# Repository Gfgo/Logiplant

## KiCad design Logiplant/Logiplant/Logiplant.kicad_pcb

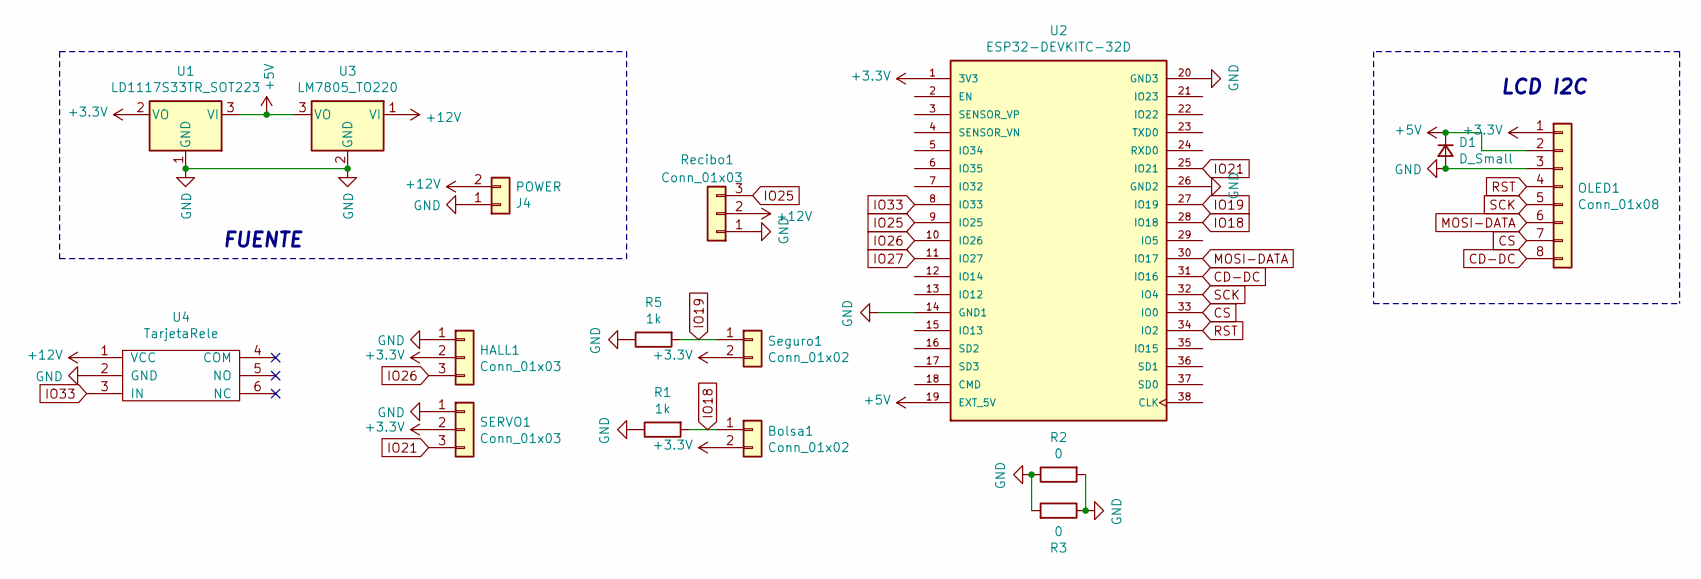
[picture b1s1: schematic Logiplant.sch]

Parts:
Bolsa1: Conn_01x02; PinHeader_1x02_P2.54mm_Vertical
D1: D_Small; D_A-405_P5.08mm_Vertical_KathodeUp
HALL1: Conn_01x03; PinHeader_1x03_P2.54mm_Vertical
J4: POWER; TerminalBlock_Phoenix_MKDS-1,5-2-5.08_1x02_P5.08mm_Horizont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
OLED1: Conn_01x08; OLED128X128
R1, R5: 1k; R_Axial_DIN0207_L6.3mm_D2.5mm_P5.08mm_Vertical
R2, R3: 0; R_Axial_DIN0207_L6.3mm_D2.5mm_P10.16mm_Horizontal
Recibo1: Conn_01x03; TerminalBlock_Phoenix_MKDS-1,5-3-5.08_1x03_P5.08mm_Horizont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
SERVO1: Conn_01x03; PinHeader_1x03_P2.54mm_Vertical
Seguro1: Conn_01x02; PinHeader_1x02_P2.54mm_Vertical
U1: LD1117S33TR_SOT223; TO-220-3_Vertical
U2: ESP32-DEVKITC-32D; Esp32wroverD; PARTREV 4
U3: LM7805_TO220; TO-220-3_Vertical
U4: TarjetaRele; TerminalBlock_Phoenix_MKDS-1,5-3-5.08_1x03_P5.08mm_Horizont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

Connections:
+3V3: Bolsa1.2, HALL1.2, OLED1.1, SERVO1.2, Seguro1.2, U1.2 (VO), U2.1 (3V3)
+5V: D1.1 (K), OLED1.2, U1.3 (VI), U2.19 (EXT_5V), U3.3 (VO)
+12V: J4.2, Recibo1.2, U3.1 (VI), U4.1 (VCC)
CD-DC: OLED1.8, U2.31 (IO16)
CS: OLED1.7, U2.33 (IO0)
GND: D1.2 (A), HALL1.1, J4.1, OLED1.3, R1.1, R2.1, R2.2, R3.1, R3.2, R5.1, Recibo1.1, SERVO1.1, U1.1 (GND), U2.14 (GND1), U2.20 (GND3), U2.26 (GND2), U3.2 (GND), U4.2 (GND)
IO18: Bolsa1.1, R1.2, U2.28 (IO18)
IO19: R5.2, Seguro1.1, U2.27 (IO19)
IO21: SERVO1.3, U2.25 (IO21)
IO25: Recibo1.3, U2.9 (IO25)
IO26: HALL1.3, U2.10 (IO26)
IO27: U2.11 (IO27)
IO33: U2.8 (IO33), U4.3 (IN)
MOSI-DATA: OLED1.6, U2.30 (IO17)
RST: OLED1.4, U2.34 (IO2)
SCK: OLED1.5, U2.32 (IO4)

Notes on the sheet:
LCD I2C
FUENTE

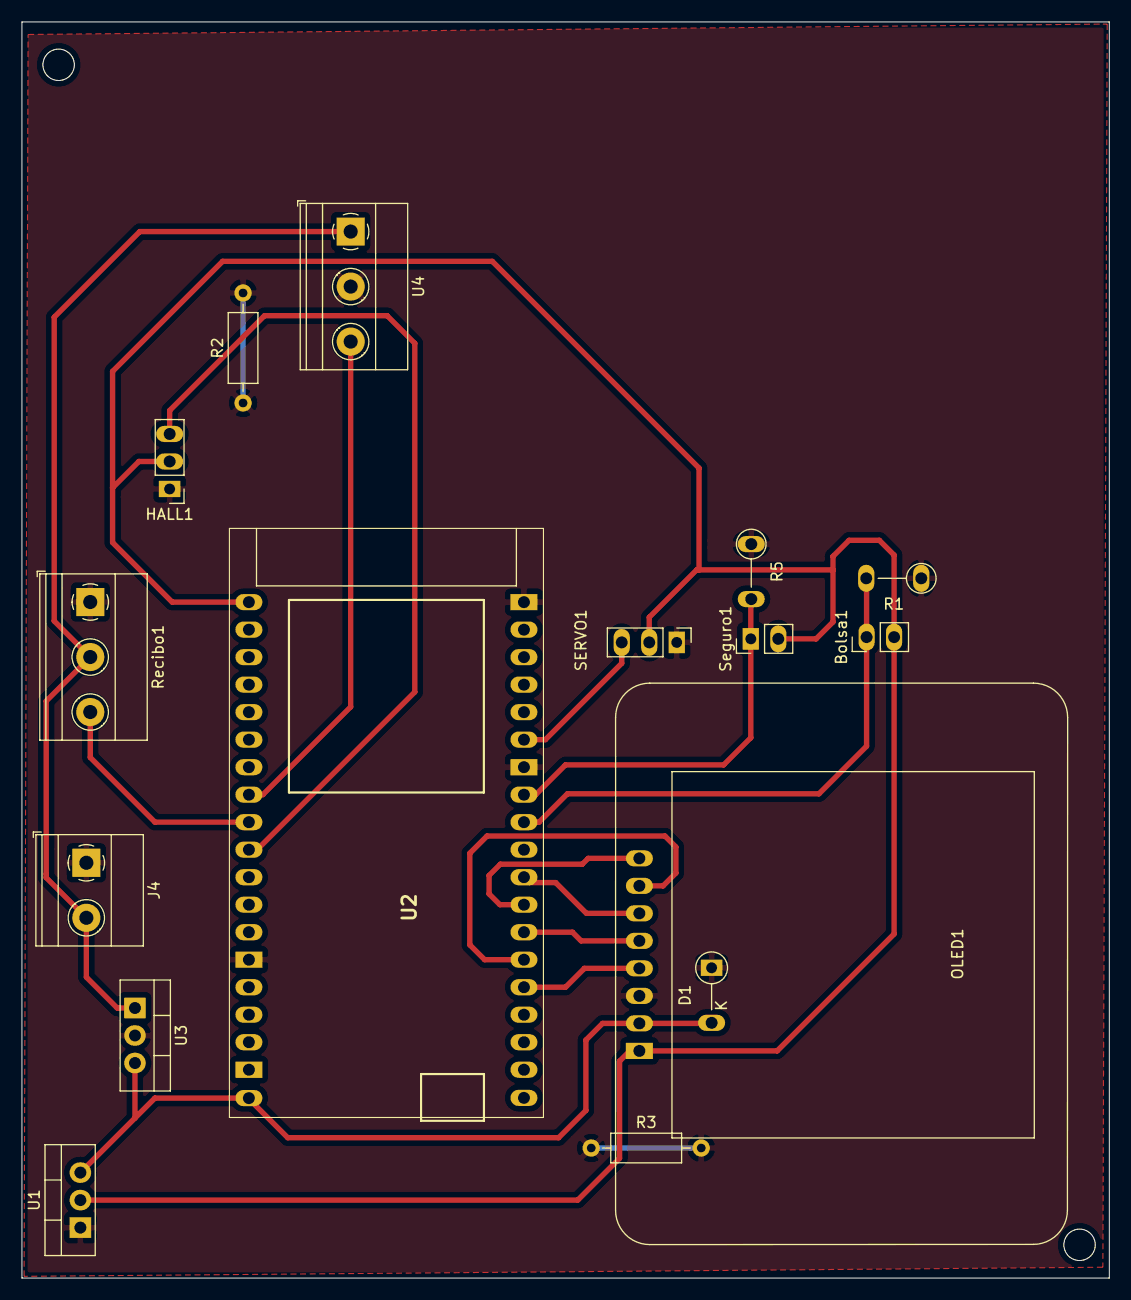
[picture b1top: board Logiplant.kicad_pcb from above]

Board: 2 copper layers, 100.4 x 116.0 mm, 16 parts (0 on the bottom side), 15 nets.

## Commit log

2022-08-02 Create Logiplant.ino
    Inicio
2022-08-10 Update Logiplant.ino
    Distancia y vibración
2023-06-20 Nuevo programa
2023-07-26 Cambio de oled
2023-09-12 Nueva regulación
2023-10-25 Nuevo prog
2023-10-26 Update Logiplant.ino
    Nuevo prog 25/10
2023-10-30 Update Logiplant.ino
    Actualización de programa falta probar todo ok y pantalla.
2023-10-31 Nuevo circuito
    Nuevo circuito
2023-11-08 circuito nuevo
    circuito
2023-11-22 Cambios PCB
2023-11-23 Actualización circuito
2024-05-22 actualización 22/05
2024-08-02 Problemas con interrupcion
    Problemas con interrupcion
2024-08-14 cambios en codigo
    cambios en codigo
2024-08-16 Update Logiplant.ino
    Botón para dar inicio ok
2024-08-16 16/08/2024 tanque lleno tiene problemas
    Seguro motor ok pero seguro tanque lleno tiene problemas
2024-08-20 Update Logiplant.ino
    seguros ok falta gsm pantalla 20/08
2024-08-21 21/08/2024 pantalla
    21/08/2024 pantalla
2024-08-22 arreglando pantalla 22/08/2024
    arreglando pantalla 22/08/2024
2024-08-23 23/08/2024
    23/08/2024 arreglar pantalla
2024-08-26 26/08/2024 arreglando pantalla
    26/08/2024 arreglando pantalla
2024-08-27 27/08/2024 falta texto
    27/08/2024 falta texto
2024-08-28 28/08/2024
    28/08/2024 PROBLEMA CON SEGUROS
2024-08-29 29/082024 problemas con programa
    29/082024 problemas con programa
2024-08-30 30/08/2024 modificar pantalla y problemas con final carrera
    30/08/2024 modificar pantalla y problemas con final carrera
2024-09-02 letras pantalla02/09/2024 pantalla e internet
    letras pantalla02/09/2024 pantalla e internet
2024-09-03 gsm y pantalla falta pruebas 03/09/2024
    gsm y pantalla falta pruebas 03/09/2024
2024-09-05 03/09/2024 gsm y pantalla falta pruebas
    03/09/2024 gsm y pantalla falta pruebas
2024-11-28 28/11/2024
    28/11/2024 Cambios en circuito
2024-12-04 3/12/2024
    3/12/2024actualizacion codigo
